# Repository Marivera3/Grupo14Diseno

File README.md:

# Grupo14Diseno
En este repositorio se muestran las rutinas implementadas para la Raspberry y ESP32 que realizan el proyecto "Camara Inteligente".

Además, se agrega un archivo comprimido "grupo14disenos.zip" que contiene la simulación del circuito, la placa realizada (Layout), las representaciones 3D de las cajas a utilizar, source del software.

Link a archivo comprimido con archivos de diseño: https://drive.google.com/file/d/1_rqe6CxWaPa32fpDPIvRqcrTsPpg1_B3/view?usp=sharing

Link a imagen de tarjeta SD para Raspberry Pi 3B+: https://drive.google.com/file/d/1i9vpLNz8A-gCcttesEl2Yn4r0JcTFwYh/view?usp=sharing

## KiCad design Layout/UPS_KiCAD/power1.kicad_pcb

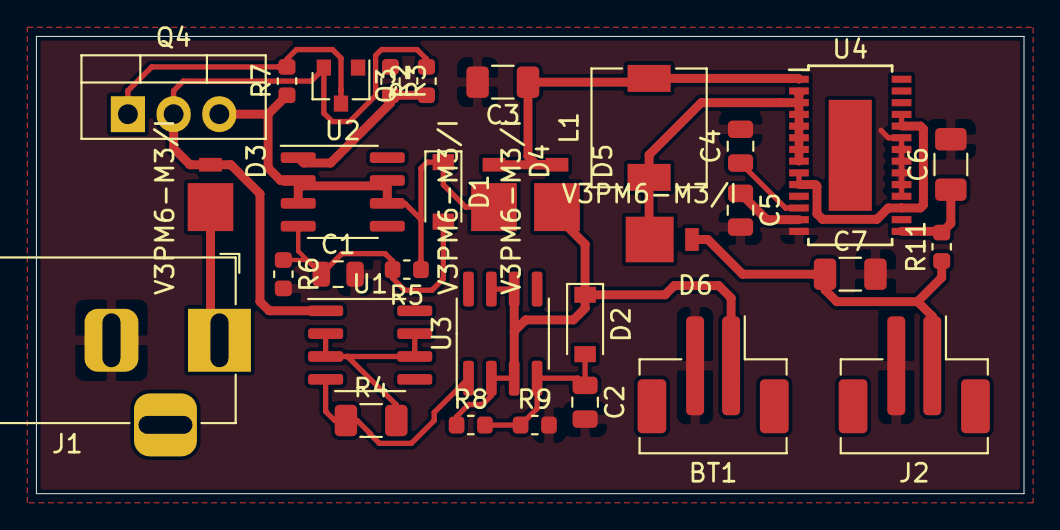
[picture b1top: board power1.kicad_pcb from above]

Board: 2 copper layers, 54.9 x 25.4 mm, 32 parts (0 on the bottom side), 19 nets.

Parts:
BT1: Battery; JST_PH_B2B-PH-SM4-TB_1x02-1MP_P2.00mm_Vertical
C1, C2, C4, C5: C; C_0805_2012Metric
C3, C6, C7: CP1; C_1206_3216Metric
D1, D2: SM4002; D_SOD-123
D3, D4, D5, D6: V3PM6-M3/I; DO-220AA
J1: Barrel_Jack; BarrelJack_Horizontal
J2: Power OUT; JST_PH_B2B-PH-SM4-TB_1x02-1MP_P2.00mm_Vertical
L1: INDUCTOR; L_6.3x6.3_H3
Q3: MMBT3906VL; SOT-23
Q4: TIP122; TO-220-3_Vertical
R2, R3, R5, R6, R7, R8, R9, R11: R_US; R_0603_1608Metric
R4: Power; R_1206_3216Metric
U1, U2, U3: LM317L_SO8; SOIC-8_3.9x4.9mm_P1.27mm
U4: MAX1709; TSSOP-28-1EP_4.4x9.7mm_P0.65mm

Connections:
GND: BT1.2, C1.2, C2.2, C3.2, C4.2, C5.2, C6.2, C7.2, J1.2, J2.2, R6.2, R9.2, U4.11, U4.14, U4.18, U4.19, U4.20, U4.21, U4.22, U4.23
unnamed: BT1.1, D2.1, D5.2, R8.1, U3.2, U3.3, U3.6, U3.7
unnamed: C1.1, D1.2, R5.2, R6.1, U2.4
unnamed: C2.1, D2.2, R8.2, R9.1, U3.4
unnamed: C3.1, D4.1, D5.1, L1.2, U4.1
unnamed: C4.1, U4.12
unnamed: C5.1, U4.13
unnamed: C6.1, R11.2, U4.15
unnamed: C7.1, D6.1, J2.1, R11.1
unnamed: D1.1, D4.2, Q4.3, R5.1, R7.1, U2.2, U2.3, U2.6, U2.7
unnamed: D3.1, Q3.2, Q4.2, R2.2, U1.1
unnamed: D3.2, J1.1
unnamed: D6.2, L1.1, U4.2, U4.3, U4.4, U4.5, U4.6, U4.7, U4.8
unnamed: Q3.1, R3.1
unnamed: Q3.3, Q4.1, R7.2
unnamed: R2.1, R3.2, U2.1
unnamed: R4.1, U1.4, U3.1
unnamed: R4.2, U1.2, U1.3, U1.6, U1.7
unnamed: U4.9, U4.10, U4.17, U4.24, U4.25

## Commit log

2020-07-18 Archivos de diseño
2020-07-18 Analisis matriz de confusion
2020-07-18 Videos de prueba
2020-07-19 Link para imagen de disco
